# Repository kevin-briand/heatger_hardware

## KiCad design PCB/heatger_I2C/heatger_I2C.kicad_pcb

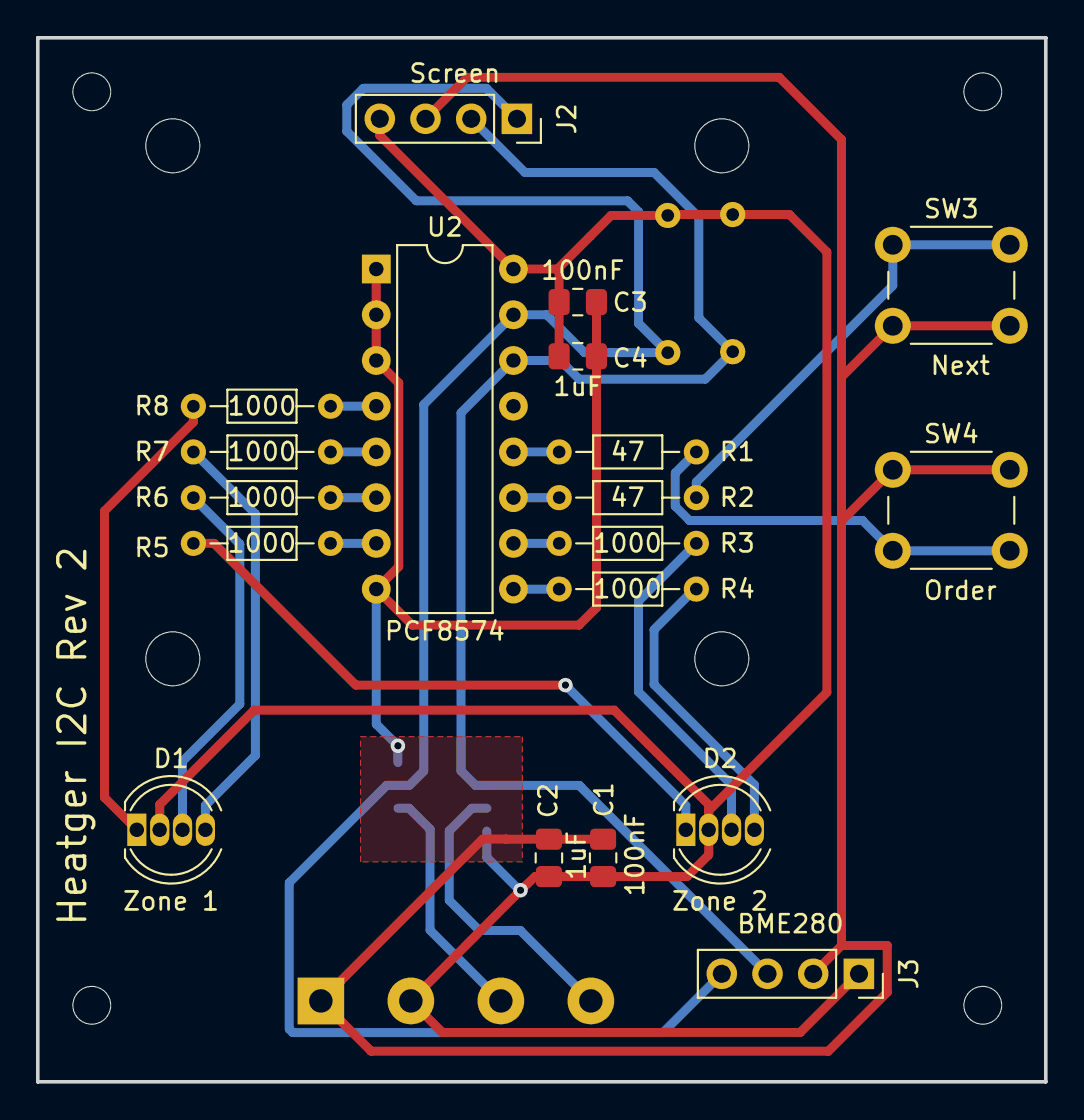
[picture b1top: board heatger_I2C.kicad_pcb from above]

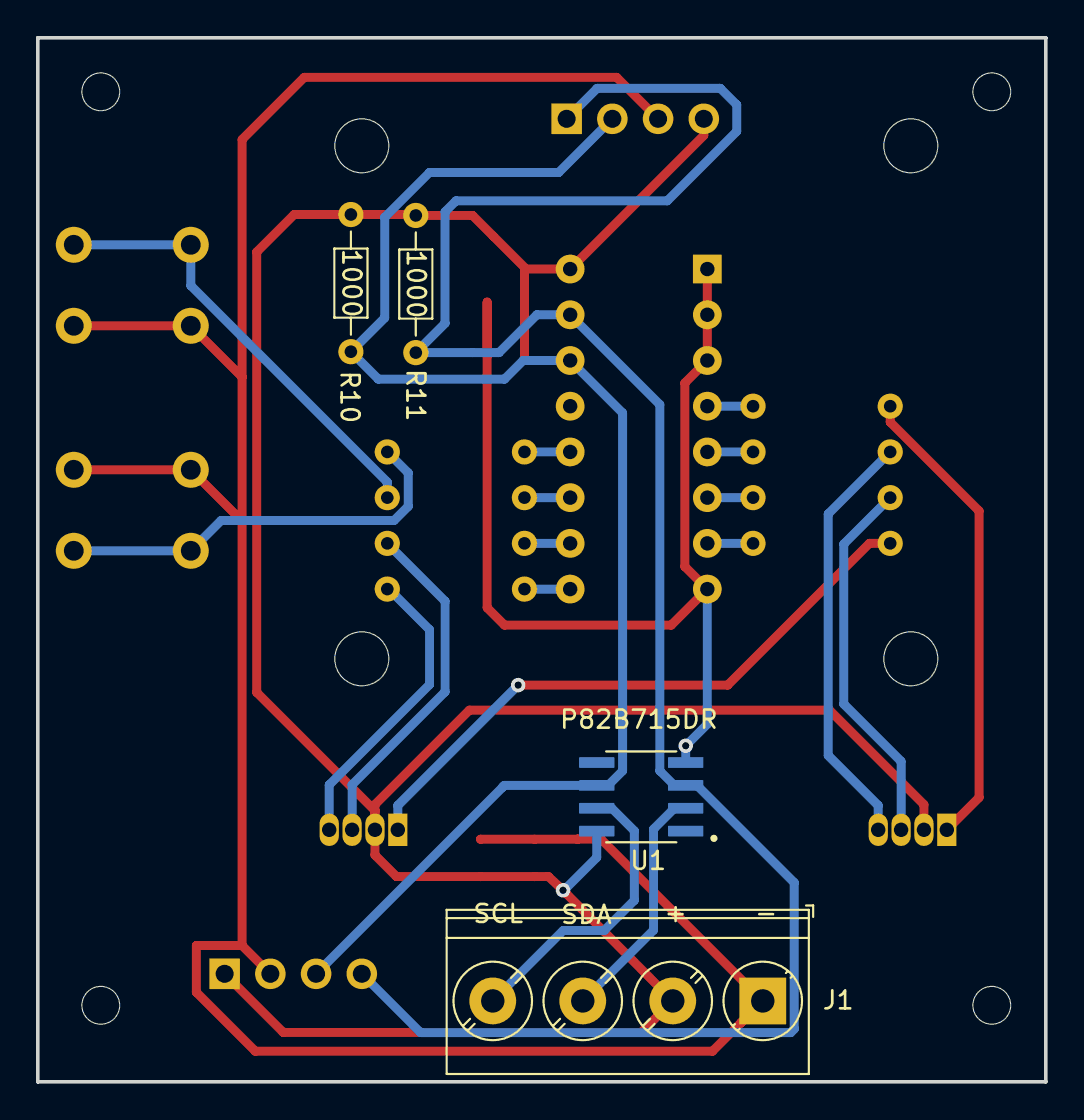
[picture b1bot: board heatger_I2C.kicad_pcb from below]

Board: 2 copper layers, 56.0 x 58.0 mm, 23 parts (4 on the bottom side), 22 nets.

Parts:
C1, C3: 100nF; C_0805_2012Metric_Pad1.18x1.45mm_HandSolder
C2, C4: 1uF; C_0805_2012Metric_Pad1.18x1.45mm_HandSolder
D1: Zone 1; LED_D5.0mm-4_RGB
D2: Zone 2; LED_D5.0mm-4_RGB
J1: TerminalBlock_Phoenix_PT-1,5-4-5.0-H_1x04_P5.00mm_Horizontal
J2: Screen; PinSocket_1x04_P2.54mm_Vertical
J3: BME280; PinSocket_1x04_P2.54mm_Vertical
R1, R2: 47; R_Axial_DIN0204_L3.6mm_D1.6mm_P7.62mm_Horizontal
R3, R4, R5, R6, R7, R8, R10, R11: 1000; R_Axial_DIN0204_L3.6mm_D1.6mm_P7.62mm_Horizontal
SW3: Next; SW_PUSH_6mm
SW4: Order; SW_PUSH_6mm
U1: P82B715DR; SOIC127P599X175-8N
U2: PCF8574; DIP-16_W7.62mm

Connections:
+5V: C1.2, C2.2, C3.1, C4.1, D1.2 (A), D2.2 (A), J1.2, J2.4, J3.1, R10.2, R11.2, U1.8 (VCC), U2.16 (VDD)
GND: C1.1, C2.1, C3.2, C4.2, J1.1, J2.3, J3.2, SW3.2, SW4.1, U1.4 (GND), U2.1 (A0), U2.2 (A1), U2.3 (A2), U2.8 (VSS)
unnamed: D1.4 (BK), R7.2
unnamed: D1.3 (GK), R6.2
unnamed: D1.1 (RK), R8.2
unnamed: D2.4 (BK), R4.2
unnamed: D2.3 (GK), R3.2
unnamed: D2.1 (RK), R5.2
unnamed: J1.3, U1.2 (LX)
unnamed: J1.4, U1.7 (LY)
unnamed: J2.1, J3.4, R11.1, U1.3 (SX), U2.15 (SDA)
unnamed: J2.2, J3.3, R10.1, U1.6 (SY), U2.14 (SCL)
unnamed: R1.2, SW4.2
unnamed: R2.2, SW3.1
unnamed: R8.1, U2.4 (P0)
unnamed: R7.1, U2.5 (P1)
unnamed: R6.1, U2.6 (P2)
unnamed: R5.1, U2.7 (P3)
unnamed: R4.1, U2.9 (P4)
unnamed: R3.1, U2.10 (P5)
unnamed: R2.1, U2.11 (P6)
unnamed: R1.1, U2.12 (P7)

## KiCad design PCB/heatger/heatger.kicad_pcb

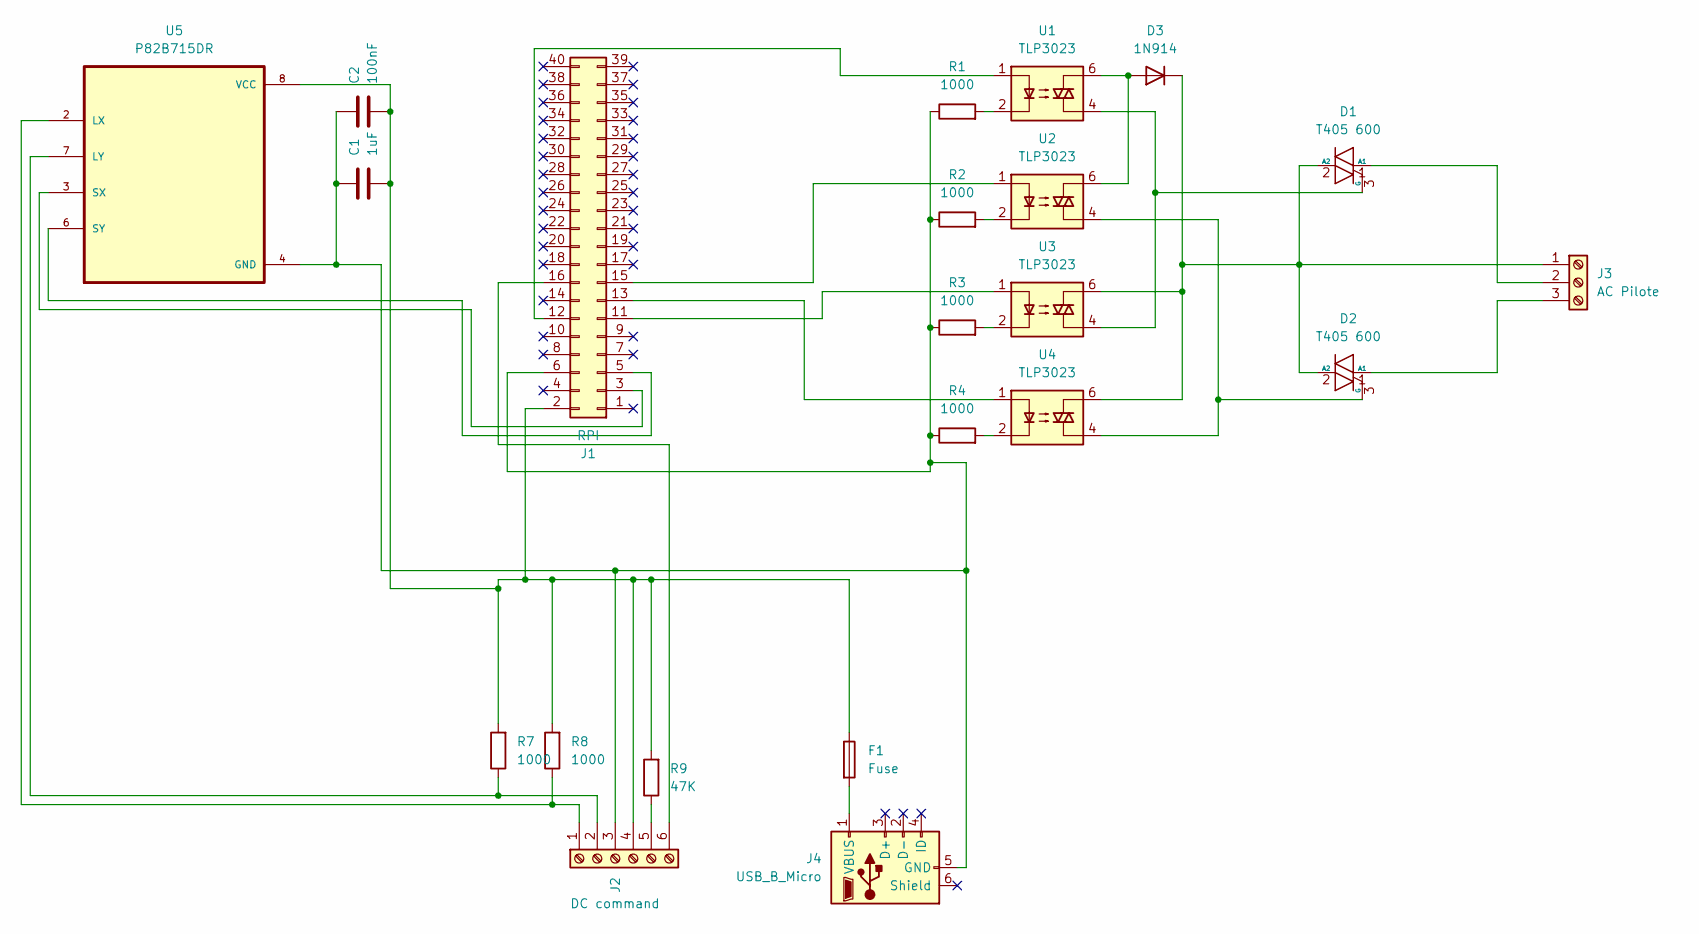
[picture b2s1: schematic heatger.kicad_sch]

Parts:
C1: 1uF; C_0805_2012Metric_Pad1.18x1.45mm_HandSolder
C2: 100nF; C_0805_2012Metric_Pad1.18x1.45mm_HandSolder
D1, D2: T405 600; VREG_L78M08CDT-TR
D3: 1N914; D_DO-35_SOD27_P7.62mm_Horizontal
F1: Fuse; Fuseholder_Cylinder-5x20mm_EATON_H15-V-1_Vertical_Closed
J1: RPI; PinSocket_2x20_P2.54mm_Vertical
J2: DC command; TerminalBlock_Phoenix_MKDS-1,5-6_1x06_P5.00mm_Horizontal
J3: AC Pilote; TerminalBlock_Phoenix_MKDS-1,5-3_1x03_P5.00mm_Horizontal
J4: USB_B_Micro; USB_Micro-B_Amphenol_10118194_Horizontal
R1, R2, R3, R4, R7, R8: 1000; R_Axial_DIN0204_L3.6mm_D1.6mm_P7.62mm_Horizontal
R9: 47K; R_Axial_DIN0204_L3.6mm_D1.6mm_P7.62mm_Horizontal
U1, U2, U3, U4: TLP3023; DIP-6_W7.62mm
U5: P82B715DR; SOIC127P599X175-8N

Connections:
unnamed: D1.1 (A1), J3.2
unnamed: D1.2 (A2), D2.2 (A2), D3.1 (K), J3.1, U3.6, U4.6
unnamed: D1.3 (G), U1.4, U3.4
unnamed: D2.1 (A1), J3.3
unnamed: D2.3 (G), U2.4, U4.4
unnamed: D3.2 (A), U1.6, U2.6
unnamed: C1.2, C2.2, F1.1, J1.2, J2.4, R7.2, R8.2, R9.2, U5.8 (VCC)
unnamed: J1.3, U5.3 (SX)
unnamed: J1.5, U5.6 (SY)
unnamed: C1.1, C2.1, J1.6, J2.3, J4.5 (GND), R1.1, R2.1, R3.1, R4.1, U5.4 (GND)
unnamed: J1.11, U3.1
unnamed: J1.12, U1.1
unnamed: J1.13, U4.1
unnamed: J1.15, U2.1
unnamed: J1.16, J2.6
unnamed: J2.1, R8.1, U5.2 (LX)
unnamed: J2.2, R7.1, U5.7 (LY)
unnamed: J2.5, R9.1
unnamed: F1.2, J4.1 (VBUS)
unnamed: R1.2, U1.2
unnamed: R2.2, U2.2
unnamed: R3.2, U3.2
unnamed: R4.2, U4.2

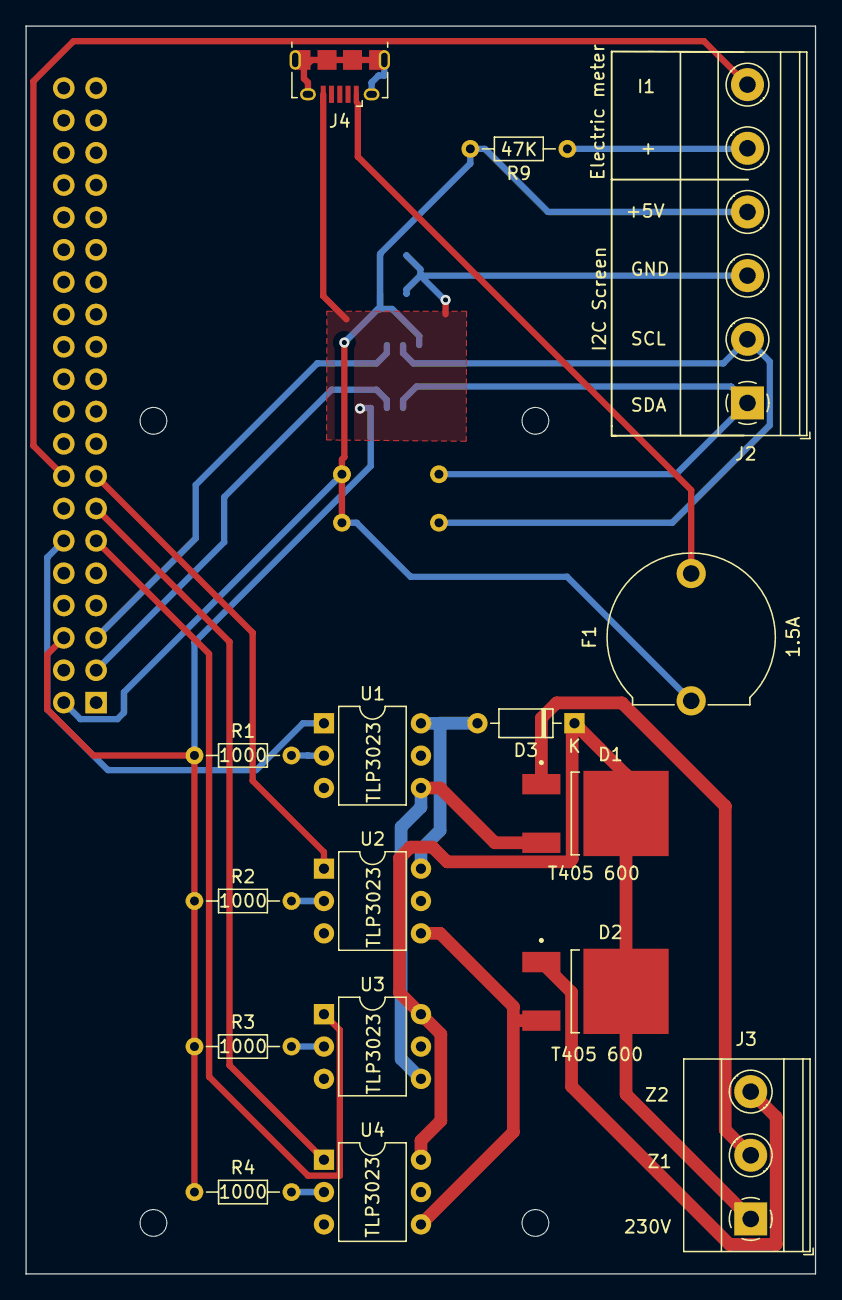
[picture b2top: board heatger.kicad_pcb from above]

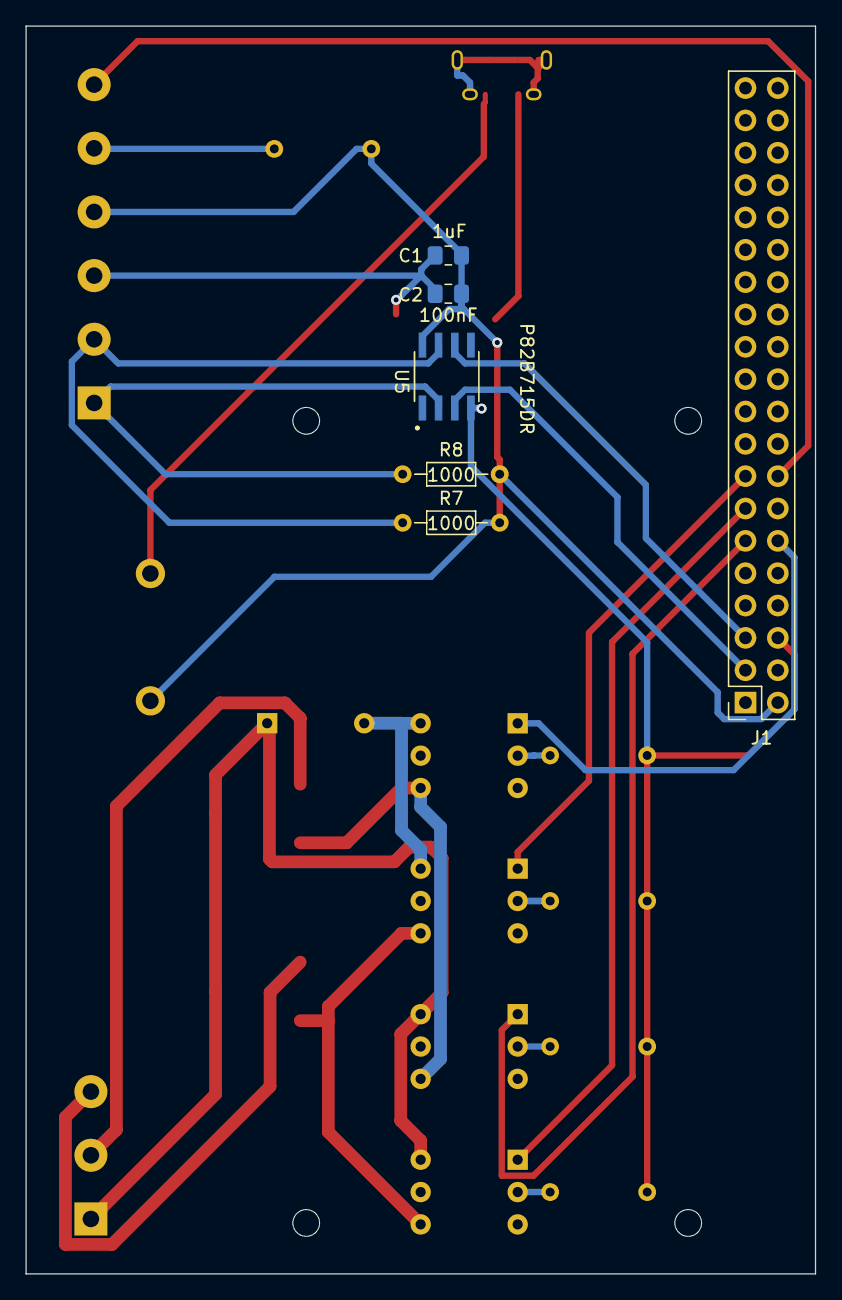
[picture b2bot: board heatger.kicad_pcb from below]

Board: 2 copper layers, 62.0 x 98.0 mm, 22 parts (6 on the bottom side), 23 nets.

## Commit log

2023-07-25 add PCB
2023-07-25 add step file
2023-07-31 add capacitors and gerbers files
2023-09-13 invert wiring for pin headers
2023-10-06 add missing route
2023-10-06 add 3d print
